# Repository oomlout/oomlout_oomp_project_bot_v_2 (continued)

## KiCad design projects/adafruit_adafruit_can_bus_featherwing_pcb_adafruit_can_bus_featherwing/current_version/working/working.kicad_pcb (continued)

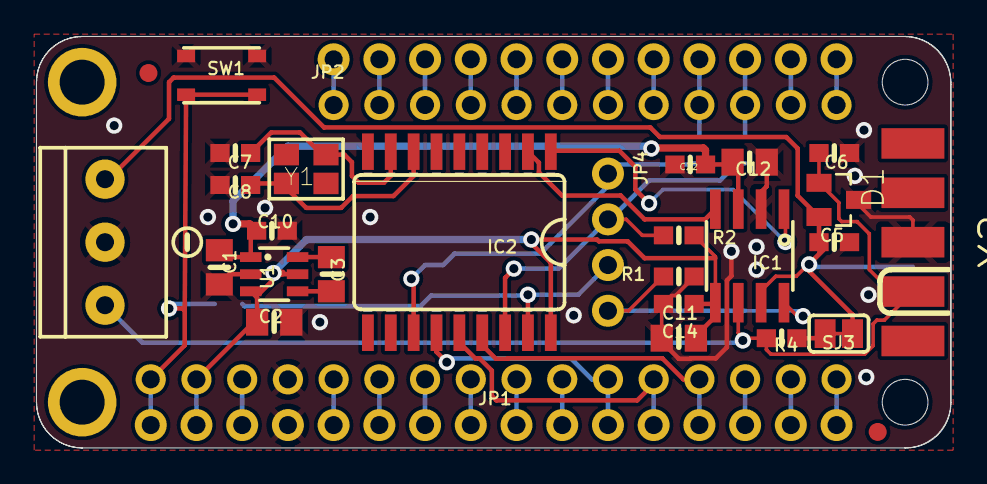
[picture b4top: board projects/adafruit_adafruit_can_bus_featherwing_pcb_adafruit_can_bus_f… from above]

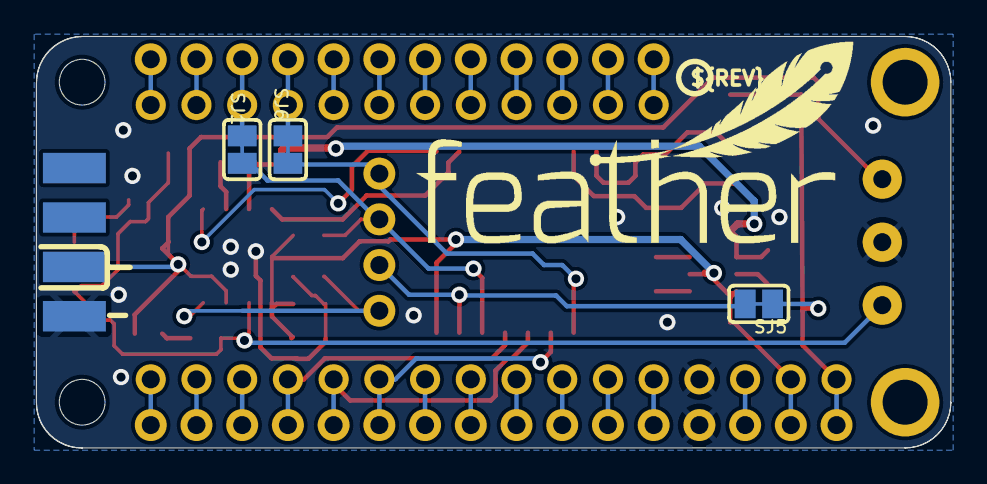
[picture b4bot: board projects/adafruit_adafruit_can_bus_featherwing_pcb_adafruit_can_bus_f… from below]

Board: 16 copper layers, 50.8 x 22.9 mm, 52 parts (12 on the bottom side), 42 nets.

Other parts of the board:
PLABEL0: PLABEL0
PLABEL1: PLABEL1
PLABEL2: PLABEL2
PLABEL3: PLABEL3
PLABEL4: PLABEL4
PLABEL5: PLABEL5
PLABEL6: PLABEL6
PLABEL8: PLABEL8
PLABEL9: PLABEL9
PLABEL10: PLABEL10
PLABEL11: PLABEL11
PLABEL12: PLABEL12
PLABEL13: PLABEL13
PLABEL14: PLABEL14
PLABEL15: PLABEL15
PLABEL16: PLABEL16
U$21: SYMBOL_MINUS
U$22: FEATHERLOGO
U$33: PCBFEAT-REV-040

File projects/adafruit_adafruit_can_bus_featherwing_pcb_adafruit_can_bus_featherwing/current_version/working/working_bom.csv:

"Id";"Designator";"Footprint";"Quantity";"Designation";"Supplier and ref";
1;"C8,C7";"0603-NO";2;"15pF";;;
2;"IC2";"SOIC18WIDE";1;"MCP2515/SO";;;
3;"C10,C22,C11";"0603-NO";3;"0.1uF";;;
4;"JP4";"1X04_ROUND";1;"";;;
5;"PLABEL15";"PLABEL15";1;"";;;
6;"NEOPIX1";"TERMBLOCK_1X3-3.5MM";1;"3.5mm";;;
7;"U1";"SOT23-6";1;"AP3602";;;
8;"C14,C12,C2,C1";"0805-NO";4;"10uF";;;
9;"FID2,FID3";"FIDUCIAL_1MM";2;"FIDUCIAL_1MM";;;
10;"Y1";"CRYSTAL_3.2X2.5";1;"16MHz 9pF";;;
11;"PLABEL2";"PLABEL2";1;"";;;
12;"U$21";"SYMBOL_MINUS";1;"";;;
13;"PLABEL3";"PLABEL3";1;"";;;
14;"PLABEL16";"PLABEL16";1;"";;;
15;"PLABEL6";"PLABEL6";1;"";;;
16;"C6,C5";"0603-NO";2;"47pF";;;
17;"SJ3,SJ1,SJ6,SJ5";"SOLDERJUMPER_CLOSEDWIRE";4;"";;;
18;"X2";"M09D";1;"DE-9";;;
19;"R2,R1";"0603-NO";2;"10K";;;
20;"MS1";"FEATHERWING_NODIM";1;"FEATHERWING_NODIM";;;
21;"JP1";"1X16_ROUND";1;"";;;
22;"SW1";"BTN_RKB2_4.6X2.8";1;"RKB2";;;
23;"IC1";"SOIC8_150MIL";1;"TJA1051T/3";;;
24;"PLABEL1";"PLABEL1";1;"";;;
25;"R4";"0603-NO";1;"120";;;
26;"D1";"SOT23";1;"PESD1CAN";;;
27;"JP2";"1X12_ROUND";1;"";;;
28;"PLABEL0";"PLABEL0";1;"";;;
29;"PLABEL4";"PLABEL4";1;"";;;
30;"PLABEL5";"PLABEL5";1;"";;;
31;"C3";"0805-NO";1;"1uF";;;
32;"PLABEL10";"PLABEL10";1;"";;;
33;"PLABEL9";"PLABEL9";1;"";;;
34;"U$33";"PCBFEAT-REV-040";1;"";;;
35;"PLABEL8";"PLABEL8";1;"";;;
36;"PLABEL11";"PLABEL11";1;"";;;
37;"PLABEL13";"PLABEL13";1;"";;;
38;"U$22";"FEATHERLOGO";1;"";;;
39;"PLABEL12";"PLABEL12";1;"";;;
40;"PLABEL14";"PLABEL14";1;"";;;

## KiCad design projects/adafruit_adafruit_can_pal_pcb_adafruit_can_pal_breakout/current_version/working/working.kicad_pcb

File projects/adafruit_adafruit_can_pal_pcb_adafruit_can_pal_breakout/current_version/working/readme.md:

# adafruit_can_pal_pcb
 
## summary 
* id: adafruit_adafruit_can_pal_pcb_adafruit_can_pal_breakout
* user: adafruit
* name: adafruit_can_pal_pcb
* board: adafruit_can_pal_breakout
* repo: https://github.com/adafruit/Adafruit-CAN-Pal-PCB

* src_file_repo_sch: 
* src_file_repo_sch_link: https://github.com/adafruit/Adafruit-CAN-Pal-PCB/tree/main/
* full details link: https://github.com/oomlout/oomlout_oomp_project_bot_v_2/tree/main/projects/adafruit_adafruit_can_pal_pcb_adafruit_can_pal_breakout/current_version/working  

## schematic  
  
[schematic (pdf)](working_schematic.pdf) 

## pcb  

[board (pdf)](working.pdf)  

## working_bom
| Id | Designator | Footprint | Quantity | Designation | Supplier and ref |  | None | 
| --- | --- | --- | --- | --- | --- | --- | --- | 
| 1 | JP2 | 1X07_ROUND_70 | 1 |  |  |  | [''] | 
| 2 | PLABEL6 | PLABEL6 | 1 |  |  |  | [''] | 
| 3 | PLABEL3 | PLABEL3 | 1 |  |  |  | [''] | 
| 4 | IC1 | SOIC8_150MIL | 1 | TJA1051T/3 |  |  | [''] | 
| 5 | C17,C16 | 0805-NO | 2 | 10uF |  |  | [''] | 
| 6 | C18 | 0805_10MGAP | 1 | 1uF |  |  | [''] | 
| 7 | U$2,U$3 | MOUNTINGHOLE_2.5_PLATED | 2 | MOUNTINGHOLE2.5 |  |  | [''] | 
| 8 | PLABEL2 | PLABEL2 | 1 |  |  |  | [''] | 
| 9 | R11,R10 | 0603-NO | 2 | 60 ohm |  |  | [''] | 
| 10 | PLABEL0 | PLABEL0 | 1 |  |  |  | [''] | 
| 11 | PLABEL4 | PLABEL4 | 1 |  |  |  | [''] | 
| 12 | PLABEL7 | PLABEL7 | 1 |  |  |  | [''] | 
| 13 | C1 | 0603-NO | 1 | 4.7nF |  |  | [''] | 
| 14 | PLABEL11 | PLABEL11 | 1 |  |  |  | [''] | 
| 15 | IC3 | SOT23-6 | 1 | AP3602 |  |  | [''] | 
| 16 | SW2 | EG1390 | 1 | EG1390 |  |  | [''] | 
| 17 | PLABEL10 | PLABEL10 | 1 |  |  |  | [''] | 
| 18 | X4 | TERMBLOCK_1X3-3.5MM | 1 | 3.5mm Terminal |  |  | [''] | 
| 19 | PLABEL8 | PLABEL8 | 1 |  |  |  | [''] | 
| 20 | PLABEL5 | PLABEL5 | 1 |  |  |  | [''] | 
| 21 | PLABEL1 | PLABEL1 | 1 |  |  |  | [''] | 
| 22 | PLABEL9 | PLABEL9 | 1 |  |  |  | [''] | 
| 23 | PLABEL14 | PLABEL14 | 1 |  |  |  | [''] | 
| 24 | PLABEL12 | PLABEL12 | 1 |  |  |  | [''] | 
| 25 | PLABEL13 | PLABEL13 | 1 |  |  |  | [''] | 
| 26 | U$6 | ADAFRUIT_3.5MM | 1 |  |  |  | [''] | 
| 27 | U$7 | PCBFEAT-REV-040 | 1 |  |  |  | [''] | 

## bom_schematic
| Ref | Qnty | Value | Cmp name | Footprint | Description | Vendor | DNP | 
| --- | --- | --- | --- | --- | --- | --- | --- | 
| C1 | 1 | 4.7nF | CAP_CERAMIC0603_NO | working:0603-NO |  |  |  | 
| C16, C17 | 2 | 10uF | CAP_CERAMIC0805-NOOUTLINE | working:0805-NO |  |  |  | 
| C18 | 1 | 1uF | CAP_CERAMIC0805_10MGAP | working:0805_10MGAP |  |  |  | 
| IC1 | 1 | TJA1051T/3 | CAN_TRANSCIEVER_TCAN1051V | working:SOIC8_150MIL |  |  |  | 
| IC3 | 1 | AP3602 | AP3602 | working:SOT23-6 |  |  |  | 
| JP2 | 1 | HEADER-1X770MIL | HEADER-1X770MIL | working:1X07_ROUND_70 |  |  |  | 
| R10, R11 | 2 | 60 ohm | RESISTOR_0603_NOOUT | working:0603-NO |  |  |  | 
| SW2 | 1 | EG1390 | SWITCH_DPDTEG1390 | working:EG1390 |  |  |  | 
| U$2, U$3 | 2 | MOUNTINGHOLE2.5 | MOUNTINGHOLE2.5 | working:MOUNTINGHOLE_2.5_PLATED |  |  |  | 
| X4 | 1 | 3.5mm Terminal | TERMBLOCK_1X3 | working:TERMBLOCK_1X3-3.5MM |  |  |  | 

## mounting_holes
| x | y | package | value | ref | size | 
| --- | --- | --- | --- | --- | --- | 
| 0.0 | 0.0 | MOUNTINGHOLE_2.5_PLATED | MOUNTINGHOLE2.5 | U$2 | m3 | 
| 15.24 | 0.0 | MOUNTINGHOLE_2.5_PLATED | MOUNTINGHOLE2.5 | U$3 | m3 |

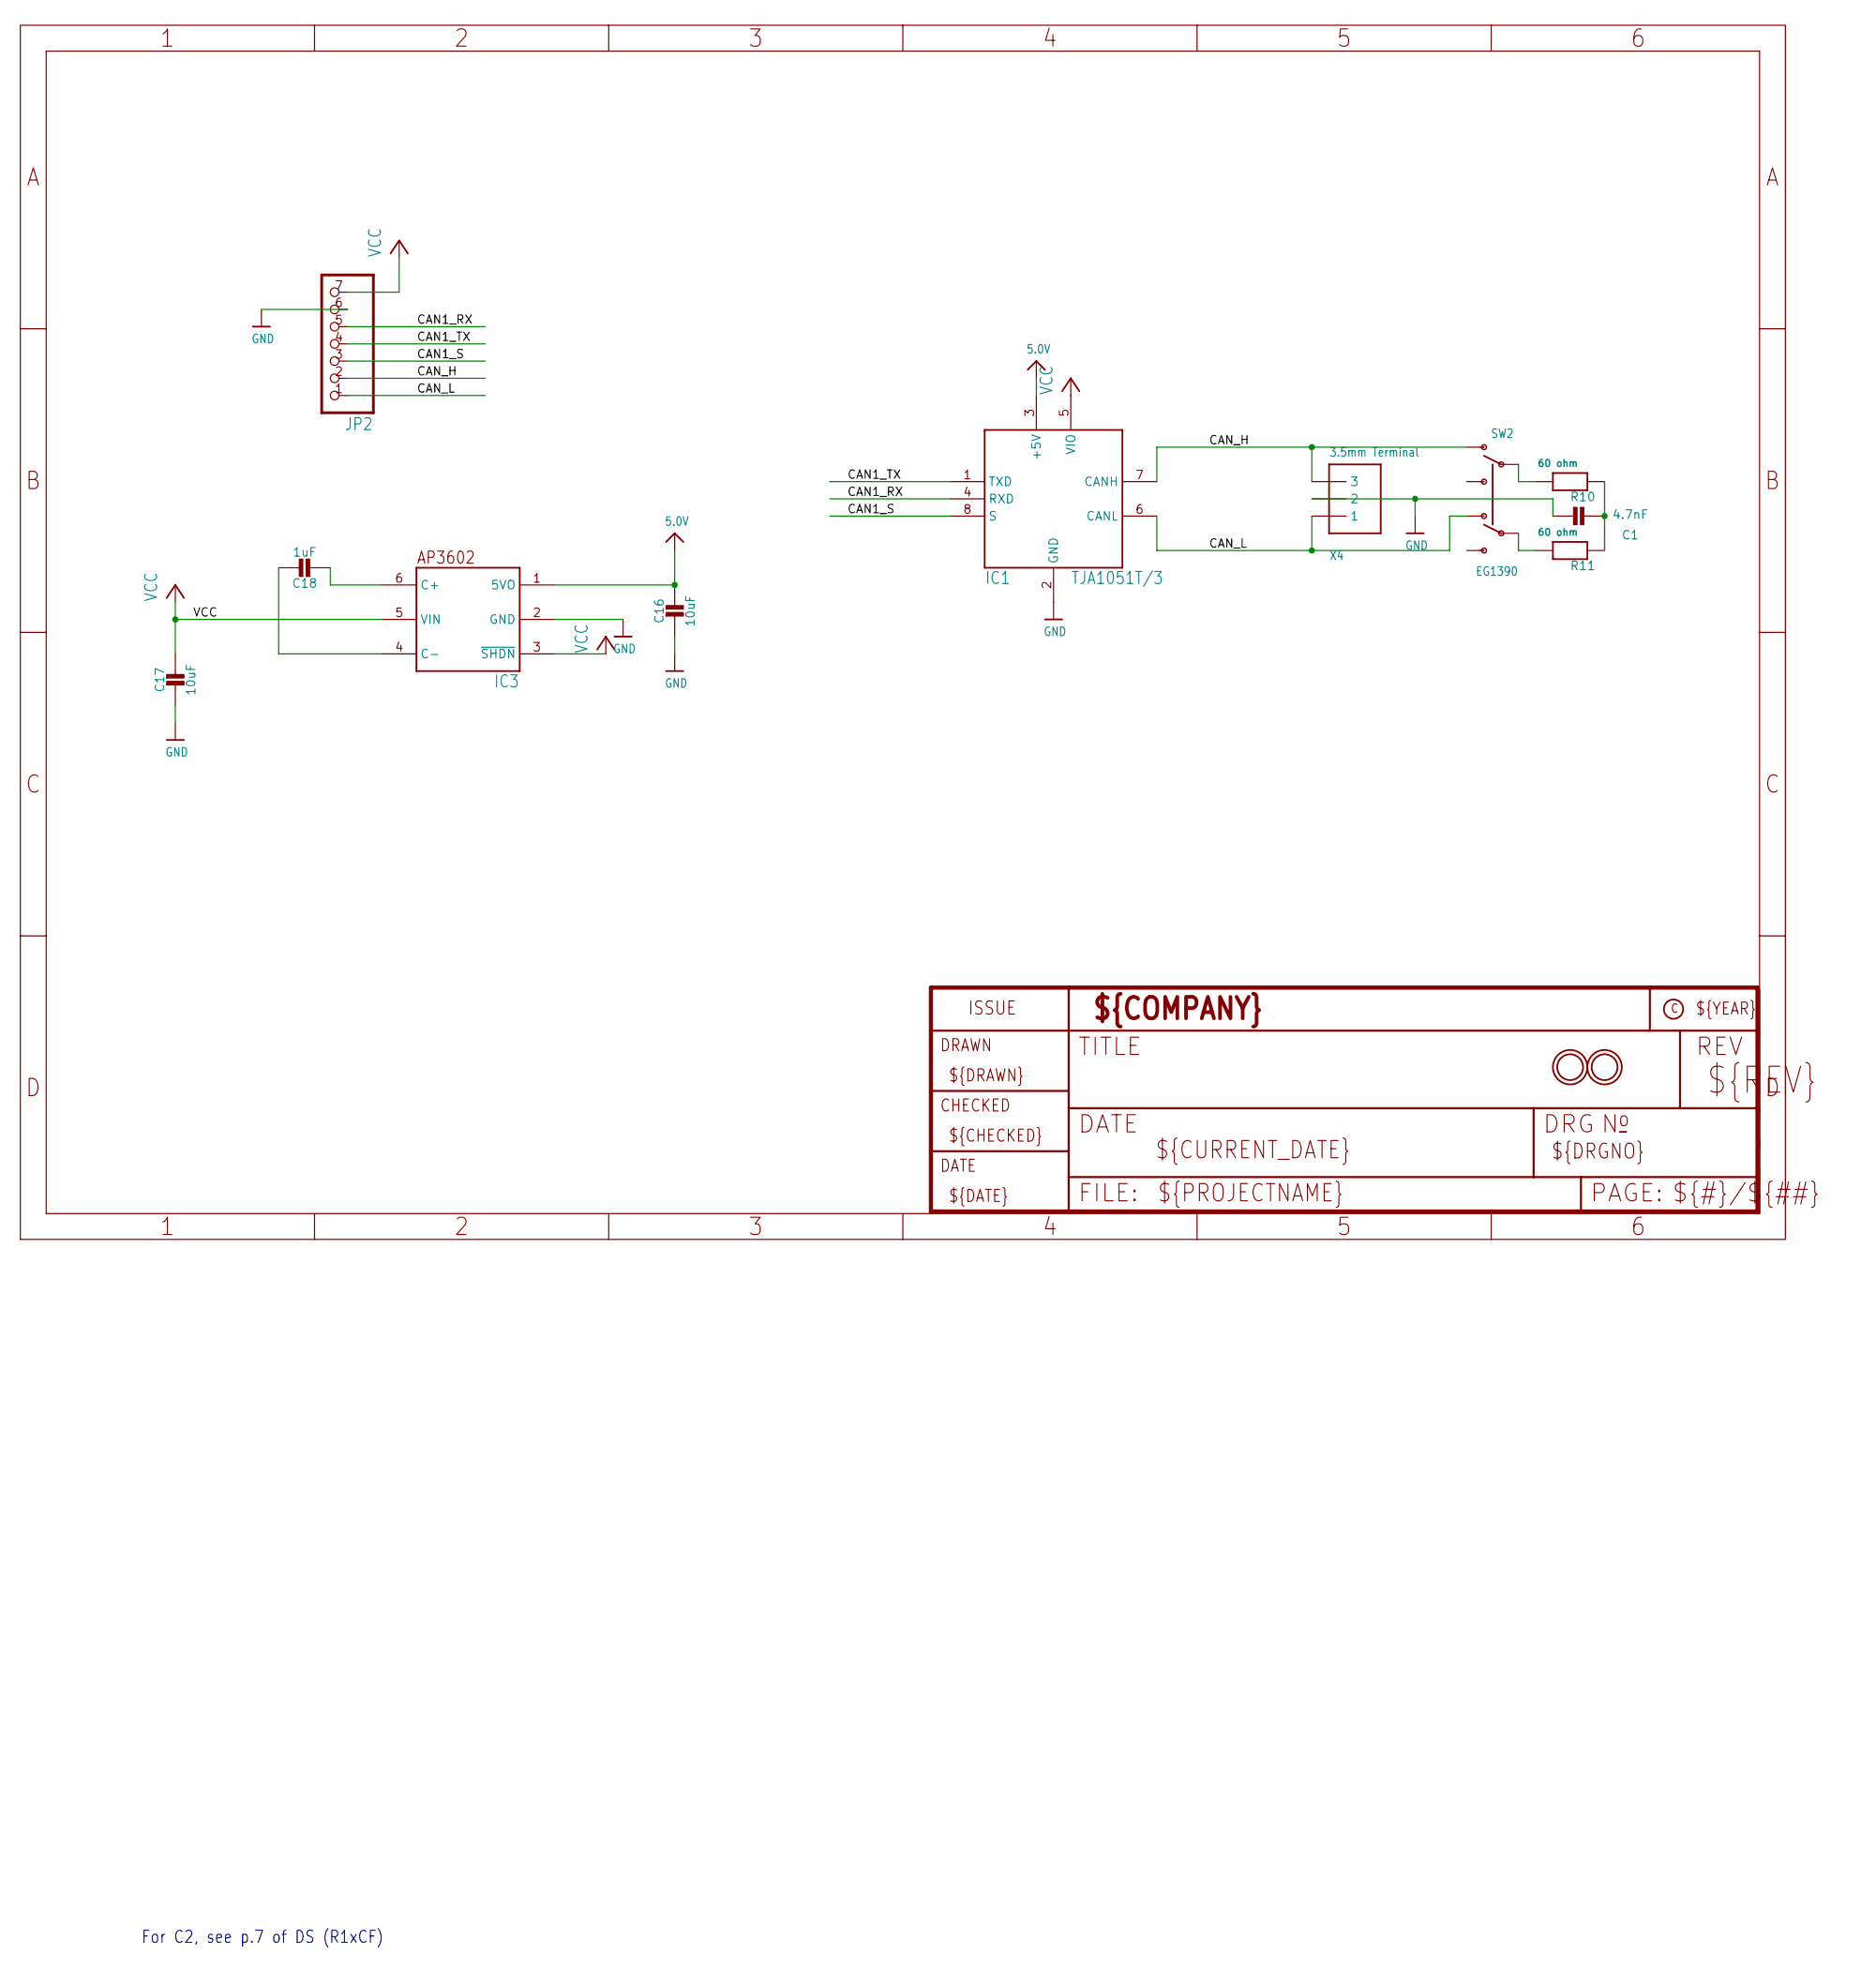
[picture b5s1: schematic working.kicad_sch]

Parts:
C1: 4.7nF; 0603-NO
C16, C17: 10uF; 0805-NO
C18: 1uF; 0805_10MGAP
IC1: TJA1051T/3; SOIC8_150MIL
IC3: AP3602; SOT23-6
JP2: HEADER-1X770MIL; 1X07_ROUND_70
R10, R11: 60 ohm; 0603-NO
SW2: EG1390
U$2, U$3: MOUNTINGHOLE2.5; MOUNTINGHOLE_2.5_PLATED
X4: 3.5mm Terminal; TERMBLOCK_1X3-3.5MM

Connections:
5.0V: C16.1, IC1.3 (+5V), IC3.1 (5VO)
CAN1_RX: IC1.4 (RXD), JP2.5
CAN1_S: IC1.8 (S), JP2.3
CAN1_TX: IC1.1 (TXD), JP2.4
CAN_H: IC1.7 (CANH), JP2.2, SW2.O1, X4.3
CAN_L: IC1.6 (CANL), JP2.1, SW2.O2, X4.1
GND: C1.2, C16.2, C17.2, IC1.2 (GND), IC3.2 (GND), JP2.6, X4.2
unnamed: R10.2, SW2.P1
unnamed: R11.2, SW2.P2
unnamed: C18.2, IC3.6 (C+)
unnamed: C18.1, IC3.4 (C-)
unnamed: C1.1, R10.1, R11.1
VCC: C17.1, IC1.5 (VIO), IC3.3 (~SHDN), IC3.5 (VIN), JP2.7

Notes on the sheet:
For C2, see p.7 of DS (R1xCF)

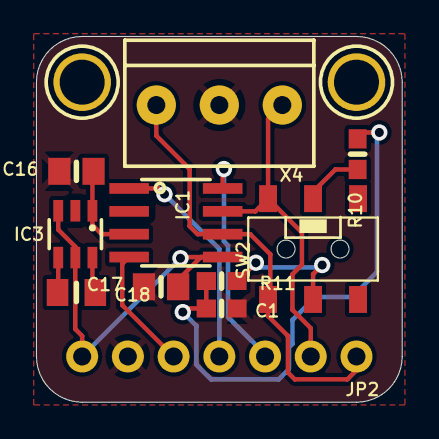
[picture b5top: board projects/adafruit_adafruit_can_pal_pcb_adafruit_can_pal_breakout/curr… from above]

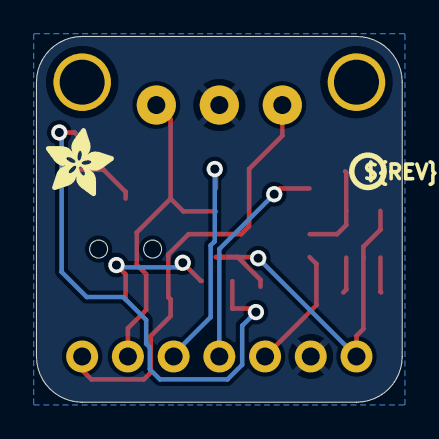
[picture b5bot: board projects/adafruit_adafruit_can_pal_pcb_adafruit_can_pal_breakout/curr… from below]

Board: 2 copper layers, 20.3 x 20.3 mm, 30 parts (5 on the bottom side), 13 nets.

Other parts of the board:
PLABEL0: PLABEL0
PLABEL1: PLABEL1
PLABEL2: PLABEL2
PLABEL3: PLABEL3
PLABEL4: PLABEL4
PLABEL5: PLABEL5
PLABEL6: PLABEL6
PLABEL7: PLABEL7
PLABEL8: PLABEL8
PLABEL9: PLABEL9
PLABEL10: PLABEL10
PLABEL11: PLABEL11
PLABEL12: PLABEL12
PLABEL13: PLABEL13
PLABEL14: PLABEL14
U$6: ADAFRUIT_3.5MM
U$7: PCBFEAT-REV-040

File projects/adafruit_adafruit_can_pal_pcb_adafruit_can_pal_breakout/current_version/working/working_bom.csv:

"Id";"Designator";"Footprint";"Quantity";"Designation";"Supplier and ref";
1;"JP2";"1X07_ROUND_70";1;"";;;
2;"PLABEL6";"PLABEL6";1;"";;;
3;"PLABEL3";"PLABEL3";1;"";;;
4;"IC1";"SOIC8_150MIL";1;"TJA1051T/3";;;
5;"C17,C16";"0805-NO";2;"10uF";;;
6;"C18";"0805_10MGAP";1;"1uF";;;
7;"U$2,U$3";"MOUNTINGHOLE_2.5_PLATED";2;"MOUNTINGHOLE2.5";;;
8;"PLABEL2";"PLABEL2";1;"";;;
9;"R11,R10";"0603-NO";2;"60 ohm";;;
10;"PLABEL0";"PLABEL0";1;"";;;
11;"PLABEL4";"PLABEL4";1;"";;;
12;"PLABEL7";"PLABEL7";1;"";;;
13;"C1";"0603-NO";1;"4.7nF";;;
14;"PLABEL11";"PLABEL11";1;"";;;
15;"IC3";"SOT23-6";1;"AP3602";;;
16;"SW2";"EG1390";1;"EG1390";;;
17;"PLABEL10";"PLABEL10";1;"";;;
18;"X4";"TERMBLOCK_1X3-3.5MM";1;"3.5mm Terminal";;;
19;"PLABEL8";"PLABEL8";1;"";;;
20;"PLABEL5";"PLABEL5";1;"";;;
21;"PLABEL1";"PLABEL1";1;"";;;
22;"PLABEL9";"PLABEL9";1;"";;;
23;"PLABEL14";"PLABEL14";1;"";;;
24;"PLABEL12";"PLABEL12";1;"";;;
25;"PLABEL13";"PLABEL13";1;"";;;
26;"U$6";"ADAFRUIT_3.5MM";1;"";;;
27;"U$7";"PCBFEAT-REV-040";1;"";;;

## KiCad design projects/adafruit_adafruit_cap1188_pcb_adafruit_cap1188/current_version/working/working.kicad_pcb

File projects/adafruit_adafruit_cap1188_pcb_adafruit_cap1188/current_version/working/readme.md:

# adafruit_cap1188_pcb
 
## summary 
* id: adafruit_adafruit_cap1188_pcb_adafruit_cap1188
* user: adafruit
* name: adafruit_cap1188_pcb
* board: adafruit_cap1188
* repo: https://github.com/adafruit/Adafruit-CAP1188-PCB

* src_file_repo_sch: 
* src_file_repo_sch_link: https://github.com/adafruit/Adafruit-CAP1188-PCB/tree/master/
* full details link: https://github.com/oomlout/oomlout_oomp_project_bot_v_2/tree/main/projects/adafruit_adafruit_cap1188_pcb_adafruit_cap1188/current_version/working  

## schematic  
  
[schematic (pdf)](working_schematic.pdf) 

## pcb  

[board (pdf)](working.pdf)  

## working_bom
| Id | Designator | Footprint | Quantity | Designation | Supplier and ref |  | None | 
| --- | --- | --- | --- | --- | --- | --- | --- | 
| 1 | U2 | SOT23-5 | 1 | MIC5225-3 |  |  | [''] | 
| 2 | LED6,LED4,LED3,LED7,LED5,LED2,LED1,LED8 | CHIPLED_0805 | 8 |  |  |  | [''] | 
| 3 | U$7,U$10,U$9,U$8 | MOUNTINGHOLE_2.0_PLATED | 4 | MOUNTINGHOLE2.0 |  |  | [''] | 
| 4 | U$13 | ADAFRUIT_3.5MM | 1 |  |  |  | [''] | 
| 5 | U1 | QFN24_4MM_SMSC | 1 |  |  |  | [''] | 
| 6 | R11,R12,R10,R9 | 0805-NO | 4 | 10K |  |  | [''] | 
| 7 | R2,R1 | RESPACK_4X0603 | 2 | 470 |  |  | [''] | 
| 8 | JP3,JP4 | 1X13_ROUND_70 | 2 |  |  |  | [''] | 
| 9 | FID2,FID1 | FIDUCIAL_1MM | 2 | FIDUCIAL" |  |  | [''] | 
| 10 | R13 | _0805MP | 1 | 150K |  |  | [''] | 
| 11 | C2,C3 | 0805-NO | 2 | 10uF |  |  | [''] | 
| 12 | U$14 | ADAFRUIT_9MM | 1 |  |  |  | [''] | 

## bom_schematic
| Ref | Qnty | Value | Cmp name | Footprint | Description | Vendor | DNP | 
| --- | --- | --- | --- | --- | --- | --- | --- | 
| C2, C3 | 2 | 10uF | CAP_CERAMIC0805-NOOUTLINE | working:0805-NO |  |  |  | 
| FID1, FID2 | 2 | FIDUCIAL"" | FIDUCIAL{dblquote}{dblquote} | working:FIDUCIAL_1MM |  |  |  | 
| JP3, JP4 | 2 | HEADER-1X13 | HEADER-1X13 | working:1X13_ROUND_70 |  |  |  | 
| LED1, LED2, LED3, LED4, LED5, LED6, LED7, LED8 | 8 | LED0805 | LED0805 | working:CHIPLED_0805 |  |  |  | 
| R1, R2 | 2 | 470 | RESISTOR_4PACK | working:RESPACK_4X0603 |  |  |  | 
| R9, R10, R11, R12 | 4 | 10K | RESISTOR0805_NOOUTLINE | working:0805-NO |  |  |  | 
| R13 | 1 | 150K | RESISTOR_0805MP | working:_0805MP |  |  |  | 
| U1 | 1 | CAP1188 | CAP1188 | working:QFN24_4MM_SMSC |  |  |  | 
| U2 | 1 | MIC5225-3 | VREG_SOT23-5 | working:SOT23-5 |  |  |  | 
| U$7, U$8, U$9, U$10 | 4 | MOUNTINGHOLE2.0 | MOUNTINGHOLE2.0 | working:MOUNTINGHOLE_2.0_PLATED |  |  |  | 

## mounting_holes
| x | y | package | value | ref | size | 
| --- | --- | --- | --- | --- | --- | 
| 0.0 | 0.0 | MOUNTINGHOLE_2.0_PLATED | MOUNTINGHOLE2.0 | U$7 | m3 | 
| 12.7 | 0.0 | MOUNTINGHOLE_2.0_PLATED | MOUNTINGHOLE2.0 | U$8 | m3 | 
| 0.0 | 36.83 | MOUNTINGHOLE_2.0_PLATED | MOUNTINGHOLE2.0 | U$9 | m3 | 
| 12.7 | 36.83 | MOUNTINGHOLE_2.0_PLATED | MOUNTINGHOLE2.0 | U$10 | m3 |

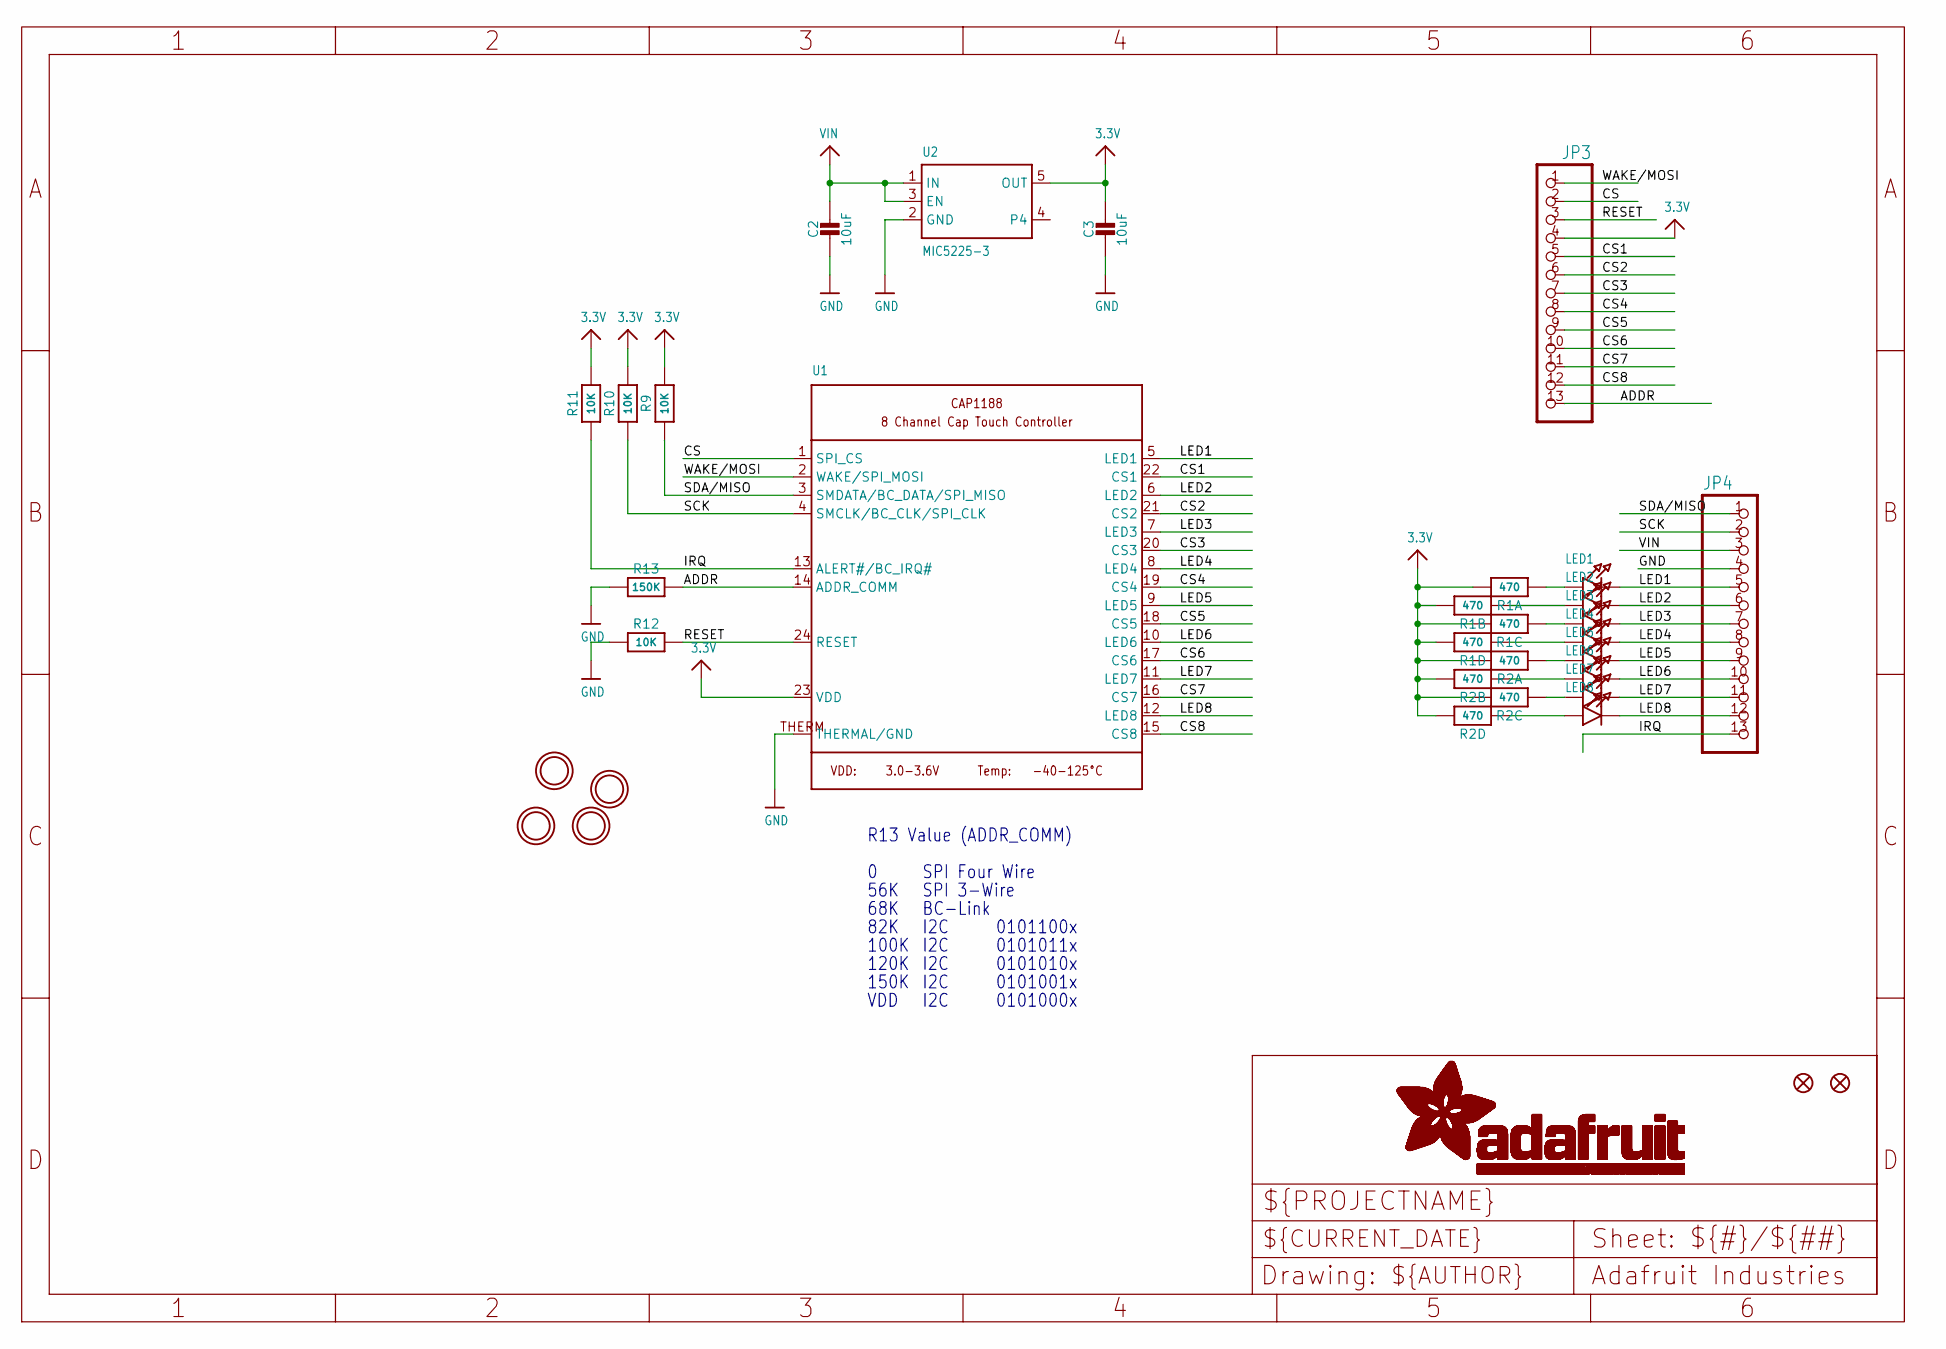
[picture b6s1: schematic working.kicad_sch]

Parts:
C2, C3: 10uF; 0805-NO
FID1, FID2: FIDUCIAL""; FIDUCIAL_1MM
JP3, JP4: HEADER-1X13; 1X13_ROUND_70
LED1, LED2, LED3, LED4, LED5, LED6, LED7, LED8: LED0805; CHIPLED_0805
R1, R2: 470; RESPACK_4X0603
R9, R10, R11, R12: 10K; 0805-NO
R13: 150K; _0805MP
U1: CAP1188; QFN24_4MM_SMSC
U2: MIC5225-3; SOT23-5
U$7, U$8, U$9, U$10: MOUNTINGHOLE2.0; MOUNTINGHOLE_2.0_PLATED

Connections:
3.3V: C3.1, JP3.4, R1.5 (2), R1.6 (2), R1.7 (2), R1.8 (2), R2.5 (2), R2.6 (2), R2.7 (2), R2.8 (2), R9.2, R10.2, R11.2, U1.23 (VDD), U2.5 (OUT)
ADDR: JP3.13, R13.2, U1.14 (ADDR_COMM)
CS: JP3.2, U1.1 (SPI_CS)
CS1: JP3.5, U1.22 (CS1)
CS2: JP3.6, U1.21 (CS2)
CS3: JP3.7, U1.20 (CS3)
CS4: JP3.8, U1.19 (CS4)
CS5: JP3.9, U1.18 (CS5)
CS6: JP3.10, U1.17 (CS6)
CS7: JP3.11, U1.16 (CS7)
CS8: JP3.12, U1.15 (CS8)
GND: C2.2, C3.2, JP4.4, R12.1, R13.1, U1.THERM (THERMAL/GND), U2.2 (GND)
IRQ: JP4.13, R11.1, U1.13 (ALERT#/BC_IRQ#)
LED1: JP4.5, LED1.C, U1.5 (LED1)
LED2: JP4.6, LED2.C, U1.6 (LED2)
LED3: JP4.7, LED3.C, U1.7 (LED3)
LED4: JP4.8, LED4.C, U1.8 (LED4)
LED5: JP4.9, LED5.C, U1.9 (LED5)
LED6: JP4.10, LED6.C, U1.10 (LED6)
LED7: JP4.11, LED7.C, U1.11 (LED7)
LED8: JP4.12, LED8.C, U1.12 (LED8)
unnamed: LED1.A, R1.1
unnamed: LED2.A, R1.2 (1)
unnamed: LED3.A, R1.3 (1)
unnamed: LED4.A, R1.4 (1)
unnamed: LED5.A, R2.1
unnamed: LED6.A, R2.2 (1)
unnamed: LED7.A, R2.3 (1)
unnamed: LED8.A, R2.4 (1)
RESET: JP3.3, R12.2, U1.24 (RESET)
SCK: JP4.2, R10.1, U1.4 (SMCLK/BC_CLK/SPI_CLK)
SDA/MISO: JP4.1, R9.1, U1.3 (SMDATA/BC_DATA/SPI_MISO)
VIN: C2.1, JP4.3, U2.1 (IN), U2.3 (EN)
WAKE/MOSI: JP3.1, U1.2 (WAKE/SPI_MOSI)

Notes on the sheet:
0101011x
82K
0101010x
56K
120K
I2C
BC-Link
0101100x
100K
SPI 3-Wire
R13 Value (ADDR_COMM)
SPI Four Wire
68K
0101001x
150K
VDD
0101000x

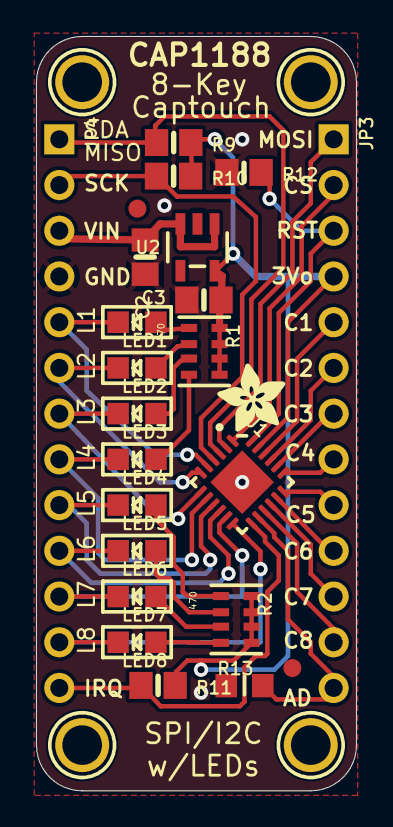
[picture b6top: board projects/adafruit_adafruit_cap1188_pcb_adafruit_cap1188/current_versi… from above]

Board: 2 copper layers, 17.8 x 41.9 mm, 29 parts (1 on the bottom side), 34 nets.

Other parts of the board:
U$13: ADAFRUIT_3.5MM
U$14: ADAFRUIT_9MM

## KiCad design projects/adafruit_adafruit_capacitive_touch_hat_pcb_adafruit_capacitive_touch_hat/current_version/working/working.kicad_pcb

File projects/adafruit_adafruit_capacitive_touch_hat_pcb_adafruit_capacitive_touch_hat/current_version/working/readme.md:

# adafruit_capacitive_touch_hat_pcb
 
## summary 
* id: adafruit_adafruit_capacitive_touch_hat_pcb_adafruit_capacitive_touch_hat
* user: adafruit
* name: adafruit_capacitive_touch_hat_pcb
* board: adafruit_capacitive_touch_hat
* repo: https://github.com/adafruit/Adafruit-Capacitive-Touch-HAT-PCB

* src_file_repo_sch: 
* src_file_repo_sch_link: https://github.com/adafruit/Adafruit-Capacitive-Touch-HAT-PCB/tree/master/
* full details link: https://github.com/oomlout/oomlout_oomp_project_bot_v_2/tree/main/projects/adafruit_adafruit_capacitive_touch_hat_pcb_adafruit_capacitive_touch_hat/current_version/working  

## schematic  
  
[schematic (pdf)](working_schematic.pdf) 

## pcb  

[board (pdf)](working.pdf)  

## working_bom
| Id | Designator | Footprint | Quantity | Designation | Supplier and ref |  | None | 
| --- | --- | --- | --- | --- | --- | --- | --- | 
| 1 | C4,C3 | 0805-NO | 2 | 0.1uF |  |  | [''] | 
| 2 | U$5 | PIHATLOGO | 1 |  |  |  | [''] | 
| 3 | JP5,ADDR0,JP4,JP6,UNK#26,JP3,JP1,IRQ0,JP7,JP12,JP10,JP8,JP11,JP2,JP9 | 1X01_ROUND | 15 |  |  |  | [''] | 
| 4 | AL4,AL2,AL8,AL6,AL12,AL5,AL11,AL1,AL3,AL9,AL10,AL7 | ALLIGATORCLIP | 12 | ALLIGATORCLIP_MICRO |  |  | [''] | 
| 5 | SJ1 | SOLDERJUMPER_CLOSEDWIRE | 1 | WP |  |  | [''] | 
| 6 | U$51 | ADAFRUIT_5MM | 1 |  |  |  | [''] | 
| 7 | C1 | 0805-NO | 1 | 10uF |  |  | [''] | 
| 8 | R6 | 0805-NO | 1 | 100K |  |  | [''] | 
| 9 | R2,R3,R1 | 0805-NO | 3 | 3.9K |  |  | [''] | 
| 10 | RPI1 | PI_HAT_SLOTS | 1 | RASPBERRYPI_BPLUS_HATSLOTS |  |  | [''] | 
| 11 | R7 | 0805-NO | 1 | 1K |  |  | [''] | 
| 12 | R5 | 0805-NO | 1 | 75K |  |  | [''] | 
| 13 | D1 | CHIPLED_0805_NOOUTLINE | 1 | RED |  |  | [''] | 
| 14 | SJ2 | SOLDERJUMPER_CLOSEDWIRE | 1 |  |  |  | [''] | 
| 15 | FID2,FID1,FID3 | FIDUCIAL_1MM | 3 | FIDUCIAL" |  |  | [''] | 
| 16 | CONN1 | 1X25_ROUND_70MIL | 1 | HEADER-1X25 |  |  | [''] | 
| 17 | U2 | QFN20_3MM_NOTHERMAL | 1 | MPR121 |  |  | [''] | 
| 18 | U$6 | PCBFEAT-REV-040 | 1 |  |  |  | [''] | 
| 19 | U1 | SOIC8_150MIL | 1 | CAT24C32 |  |  | [''] | 

## bom_schematic
| Ref | Qnty | Value | Cmp name | Footprint | Description | Vendor | DNP | 
| --- | --- | --- | --- | --- | --- | --- | --- | 
| ADDR0 | 1 | HEADER-1X1ROUND | HEADER-1X1ROUND | working:1X01_ROUND |  |  |  | 
| AL1, AL2, AL3, AL4, AL5, AL6, AL7, AL8, AL9, AL10, AL11, AL12 | 12 | ALLIGATORCLIP_MICRO | ALLIGATORCLIP_MICRO | working:ALLIGATORCLIP |  |  |  | 
| C1 | 1 | 10uF | CAP_CERAMIC0805-NOOUTLINE | working:0805-NO |  |  |  | 
| C3, C4 | 2 | 0.1uF | CAP_CERAMIC0805-NOOUTLINE | working:0805-NO |  |  |  | 
| CONN1 | 1 | HEADER-1X25 | HEADER-1X25 | working:1X25_ROUND_70MIL |  |  |  | 
| D1 | 1 | RED | LED0805_NOOUTLINE | working:CHIPLED_0805_NOOUTLINE |  |  |  | 
| FID1, FID2, FID3 | 3 | FIDUCIAL"" | FIDUCIAL{dblquote}{dblquote} | working:FIDUCIAL_1MM |  |  |  | 
| IRQ0 | 1 | HEADER-1X1ROUND | HEADER-1X1ROUND | working:1X01_ROUND |  |  |  | 
| JP1, JP2, JP3, JP4, JP5, JP6, JP7, JP8, JP9, JP10, JP11, JP12 | 12 | HEADER-1X1ROUND | HEADER-1X1ROUND | working:1X01_ROUND |  |  |  | 
| R1, R2, R3 | 3 | 3.9K | RESISTOR0805_NOOUTLINE | working:0805-NO |  |  |  | 
| R5 | 1 | 75K | RESISTOR0805_NOOUTLINE | working:0805-NO |  |  |  | 
| R6 | 1 | 100K | RESISTOR0805_NOOUTLINE | working:0805-NO |  |  |  | 
| R7 | 1 | 1K | RESISTOR0805_NOOUTLINE | working:0805-NO |  |  |  | 
| RPI1 | 1 | RASPBERRYPI_BPLUS_HATSLOTS | RASPBERRYPI_BPLUS_HATSLOTS | working:PI_HAT_SLOTS |  |  |  | 
| SJ1 | 1 | WP | SOLDERJUMPER_CLOSED | working:SOLDERJUMPER_CLOSEDWIRE |  |  |  | 
| SJ2 | 1 | SOLDERJUMPER_CLOSED | SOLDERJUMPER_CLOSED | working:SOLDERJUMPER_CLOSEDWIRE |  |  |  | 
| U1 | 1 | CAT24C32 | EEPROM_I2C_SOIC8_GENERIC | working:SOIC8_150MIL |  |  |  | 
| U2 | 1 | MPR121 | MPR121Q | working:QFN20_3MM_NOTHERMAL |  |  |  | 
| UNK#26 | 1 | HEADER-1X1ROUND | HEADER-1X1ROUND | working:1X01_ROUND |  |  |  |

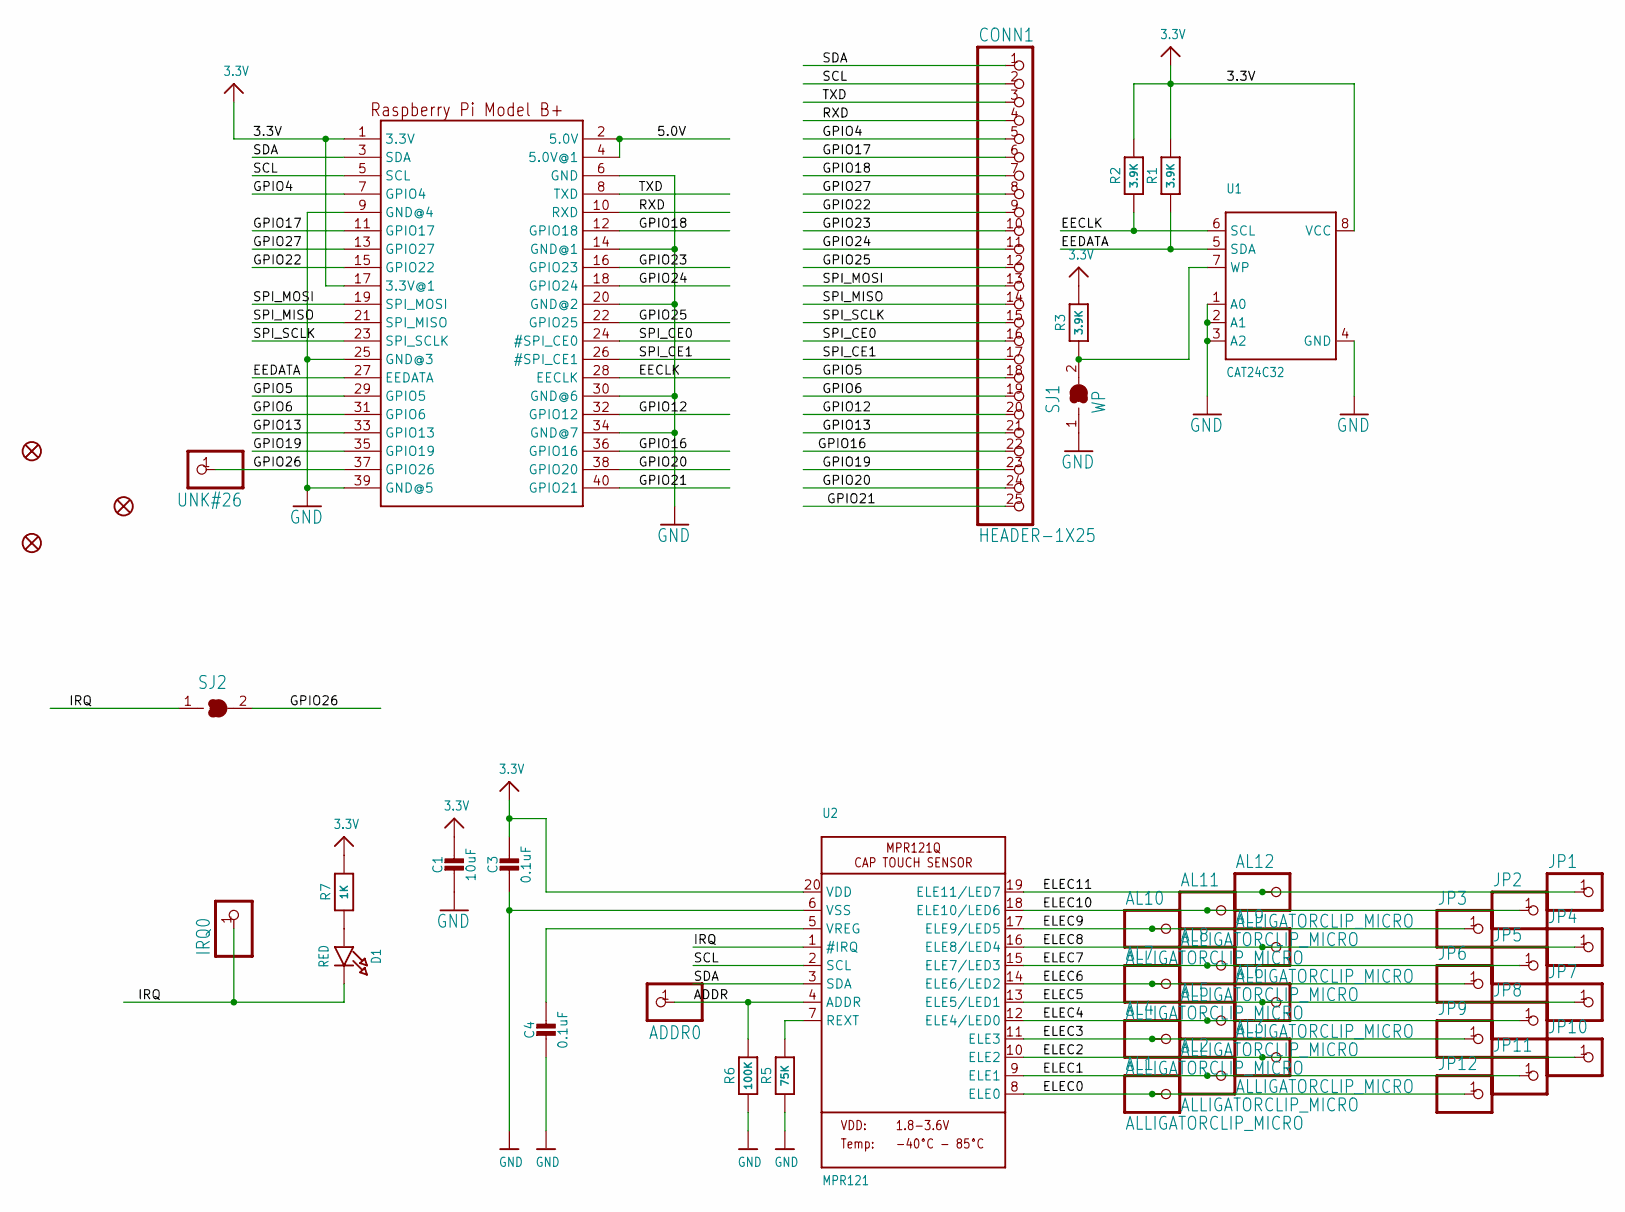
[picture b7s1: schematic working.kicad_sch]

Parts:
ADDR0: HEADER-1X1ROUND; 1X01_ROUND
AL1, AL2, AL3, AL4, AL5, AL6, AL7, AL8, AL9, AL10, AL11, AL12: ALLIGATORCLIP_MICRO; ALLIGATORCLIP
C1: 10uF; 0805-NO
C3, C4: 0.1uF; 0805-NO
CONN1: HEADER-1X25; 1X25_ROUND_70MIL
D1: RED; CHIPLED_0805_NOOUTLINE
FID1, FID2, FID3: FIDUCIAL""; FIDUCIAL_1MM
IRQ0: HEADER-1X1ROUND; 1X01_ROUND
JP1, JP2, JP3, JP4, JP5, JP6, JP7, JP8, JP9, JP10, JP11, JP12: HEADER-1X1ROUND; 1X01_ROUND
R1, R2, R3: 3.9K; 0805-NO
R5: 75K; 0805-NO
R6: 100K; 0805-NO
R7: 1K; 0805-NO
RPI1: RASPBERRYPI_BPLUS_HATSLOTS; PI_HAT_SLOTS
SJ1: WP; SOLDERJUMPER_CLOSEDWIRE
SJ2: SOLDERJUMPER_CLOSED; SOLDERJUMPER_CLOSEDWIRE
U1: CAT24C32; SOIC8_150MIL
U2: MPR121; QFN20_3MM_NOTHERMAL
UNK#26: HEADER-1X1ROUND; 1X01_ROUND

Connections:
3.3V: C1.1, C3.1, R1.2, R2.2, R3.2, R7.2, RPI1.1 (3.3V), RPI1.17 (3.3V@1), U1.8 (VCC), U2.20 (VDD)
5.0V: RPI1.2 (5.0V), RPI1.4 (5.0V@1)
ADDR: ADDR0.1, R6.2, U2.4 (ADDR)
EECLK: R2.1, RPI1.28 (EECLK), U1.6 (SCL)
EEDATA: R1.1, RPI1.27 (EEDATA), U1.5 (SDA)
ELEC0: AL1.P$1, AL1.P$2, JP12.1, U2.8 (ELE0)
ELEC1: AL2.P$1, AL2.P$2, JP11.1, U2.9 (ELE1)
ELEC2: AL3.P$1, AL3.P$2, JP10.1, U2.10 (ELE2)
ELEC3: AL4.P$1, AL4.P$2, JP9.1, U2.11 (ELE3)
ELEC4: AL5.P$1, AL5.P$2, JP8.1, U2.12 (ELE4/LED0)
ELEC5: AL6.P$1, AL6.P$2, JP7.1, U2.13 (ELE5/LED1)
ELEC6: AL7.P$1, AL7.P$2, JP6.1, U2.14 (ELE6/LED2)
ELEC7: AL8.P$1, AL8.P$2, JP5.1, U2.15 (ELE7/LED3)
ELEC8: AL9.P$1, AL9.P$2, JP4.1, U2.16 (ELE8/LED4)
ELEC9: AL10.P$1, AL10.P$2, JP3.1, U2.17 (ELE9/LED5)
ELEC10: AL11.P$1, AL11.P$2, JP2.1, U2.18 (ELE10/LED6)
ELEC11: AL12.P$1, AL12.P$2, JP1.1, U2.19 (ELE11/LED7)
GND: C1.2, C3.2, C4.2, R5.1, R6.1, RPI1.6 (GND), RPI1.9 (GND@4), RPI1.14 (GND@1), RPI1.20 (GND@2), RPI1.25 (GND@3), RPI1.30 (GND@6), RPI1.34 (GND@7), RPI1.39 (GND@5), SJ1.1, U1.1 (A0), U1.2 (A1), U1.3 (A2), U1.4 (GND), U2.6 (VSS)
GPIO4: CONN1.5, RPI1.7 (GPIO4)
GPIO5: CONN1.18, RPI1.29 (GPIO5)
GPIO6: CONN1.19, RPI1.31 (GPIO6)
GPIO12: CONN1.20, RPI1.32 (GPIO12)
GPIO13: CONN1.21, RPI1.33 (GPIO13)
GPIO16: CONN1.22, RPI1.36 (GPIO16)
GPIO17: CONN1.6, RPI1.11 (GPIO17)
GPIO18: CONN1.7, RPI1.12 (GPIO18)
GPIO19: CONN1.23, RPI1.35 (GPIO19)
GPIO20: CONN1.24, RPI1.38 (GPIO20)
GPIO21: CONN1.25, RPI1.40 (GPIO21)
GPIO22: CONN1.9, RPI1.15 (GPIO22)
GPIO23: CONN1.10, RPI1.16 (GPIO23)
GPIO24: CONN1.11, RPI1.18 (GPIO24)
GPIO25: CONN1.12, RPI1.22 (GPIO25)
GPIO26: RPI1.37 (GPIO26), SJ2.2, UNK#26.1
GPIO27: CONN1.8, RPI1.13 (GPIO27)
IRQ: D1.C, IRQ0.1, SJ2.1, U2.1 (#IRQ)
unnamed: R3.1, SJ1.2, U1.7 (WP)
unnamed: C4.1, U2.5 (VREG)
unnamed: R5.2, U2.7 (REXT)
unnamed: D1.A, R7.1
RXD: CONN1.4, RPI1.10 (RXD)
SCL: CONN1.2, RPI1.5 (SCL), U2.2 (SCL)
SDA: CONN1.1, RPI1.3 (SDA), U2.3 (SDA)
SPI_CE0: CONN1.16, RPI1.24 (#SPI_CE0)
SPI_CE1: CONN1.17, RPI1.26 (#SPI_CE1)
SPI_MISO: CONN1.14, RPI1.21 (SPI_MISO)
SPI_MOSI: CONN1.13, RPI1.19 (SPI_MOSI)
SPI_SCLK: CONN1.15, RPI1.23 (SPI_SCLK)
TXD: CONN1.3, RPI1.8 (TXD)

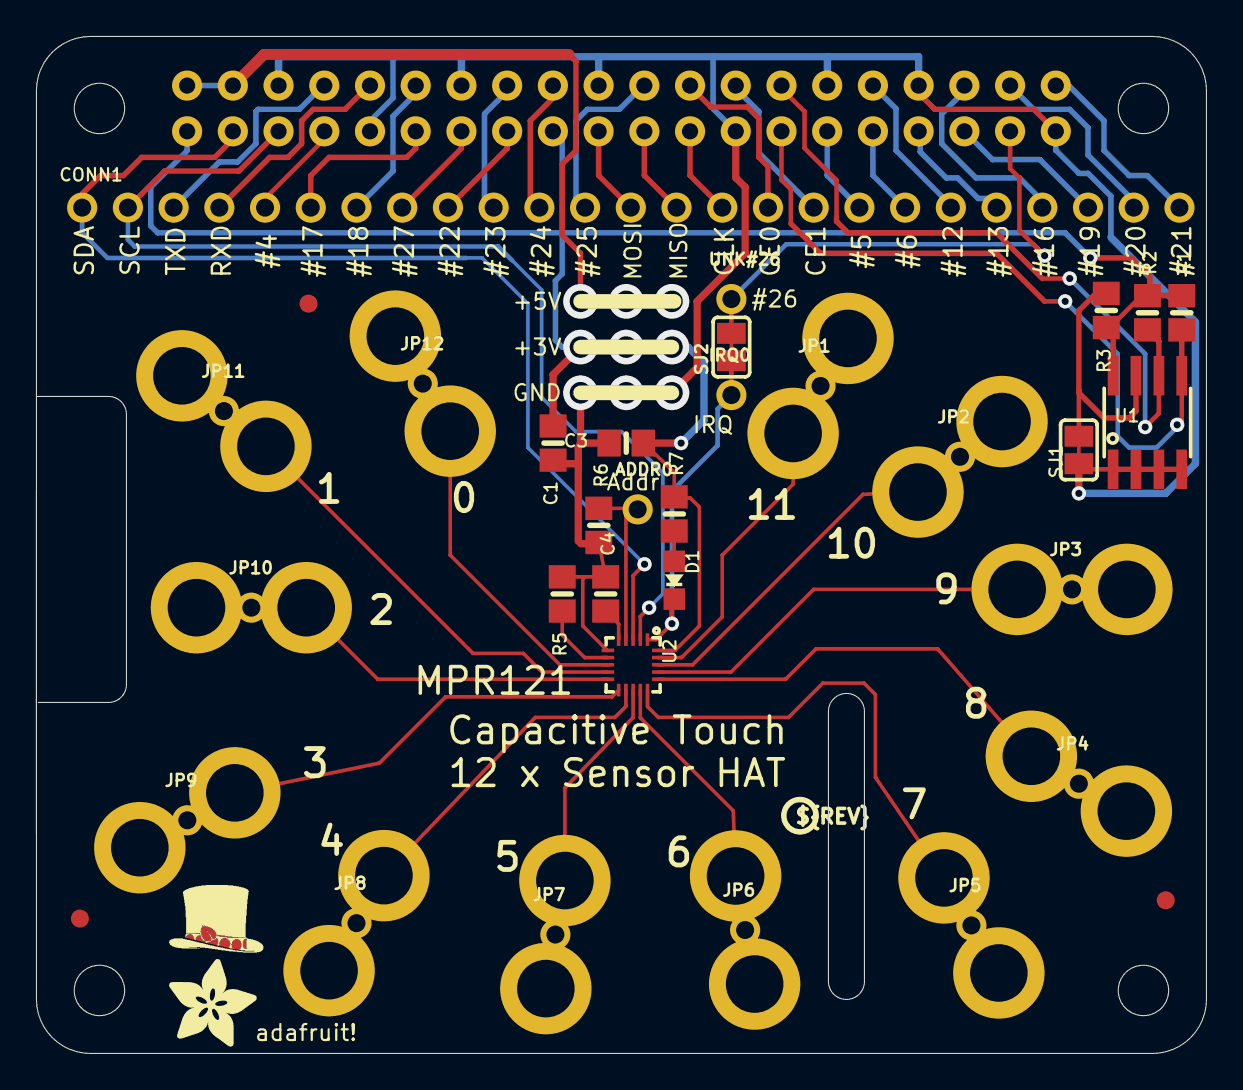
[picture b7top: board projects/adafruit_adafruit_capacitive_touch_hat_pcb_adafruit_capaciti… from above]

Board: 2 copper layers, 65.0 x 56.5 mm, 49 parts (0 on the bottom side), 49 nets.

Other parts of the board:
U$5: PIHATLOGO
U$6: PCBFEAT-REV-040
U$51: ADAFRUIT_5MM
